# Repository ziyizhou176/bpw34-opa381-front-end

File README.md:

# BPW34 + OPA381 Weak-Signal Photodetector Front-End

KiCad-based, version-controlled redesign of a weak optical signal front-end for physics competition work.

## Final V2 design target

- Photodiode: BPW34
- TIA: OPA381
- Supply input: +5 V
- Analog rail: LP5907-3.3 -> AVDD_3V3
- Reference: REF3312 -> VREF_RAW -> 10 kΩ -> VBIAS_1V25, with local 1 µF bypass
- TIA feedback: 1 MΩ || 15 pF
- ADC isolation/filter: 1 kΩ series + 33 nF to AGND
- Calibration injection: CAL_IN -> 100 MΩ -> normally-open SJCAL -> SUM
- MCU interface: +5V_IN / AGND / ADC_OUT to existing STM32G431 board
- Target modulation/detection: 1 kHz optical modulation, 20 kS/s ADC, digital lock-in / FFT in MCU

## Development policy

This repository replaces GUI-only iterative PCB editing. Every electrical/layout milestone must be committed so that schematic, PCB, and production data can be diffed and rolled back.

Planned milestones:

1. `v0.1-schematic` — clean KiCad schematic, ERC pass, footprint mapping reviewed
2. `v0.2-placement` — critical analog placement frozen
3. `v0.3-critical-routing` — SUM, feedback, VBIAS, OPA381 local decoupling completed
4. `v0.4-full-routing` — remaining power/ADC/CAL routing and ground strategy completed
5. `v1.0-production` — DRC pass, Gerber/BOM/PnP ready for fabrication

## Reference design

Layout principles will be compared against the open hardware project `TU-Darmstadt-APQ/PDH_photodiode`, especially its photodiode/TIA placement, feedback-loop minimization, local decoupling, and ground strategy. The final circuit here is not intended to be an electrical clone; it is redesigned around BPW34, OPA381, 3.3 V single-supply operation, 1.25 V bias, STM32 ADC interfacing, and the calibration network used in this project.

## Status

Repository initialized. Next step: freeze the V2 electrical specification and create the KiCad project skeleton before any PCB routing.

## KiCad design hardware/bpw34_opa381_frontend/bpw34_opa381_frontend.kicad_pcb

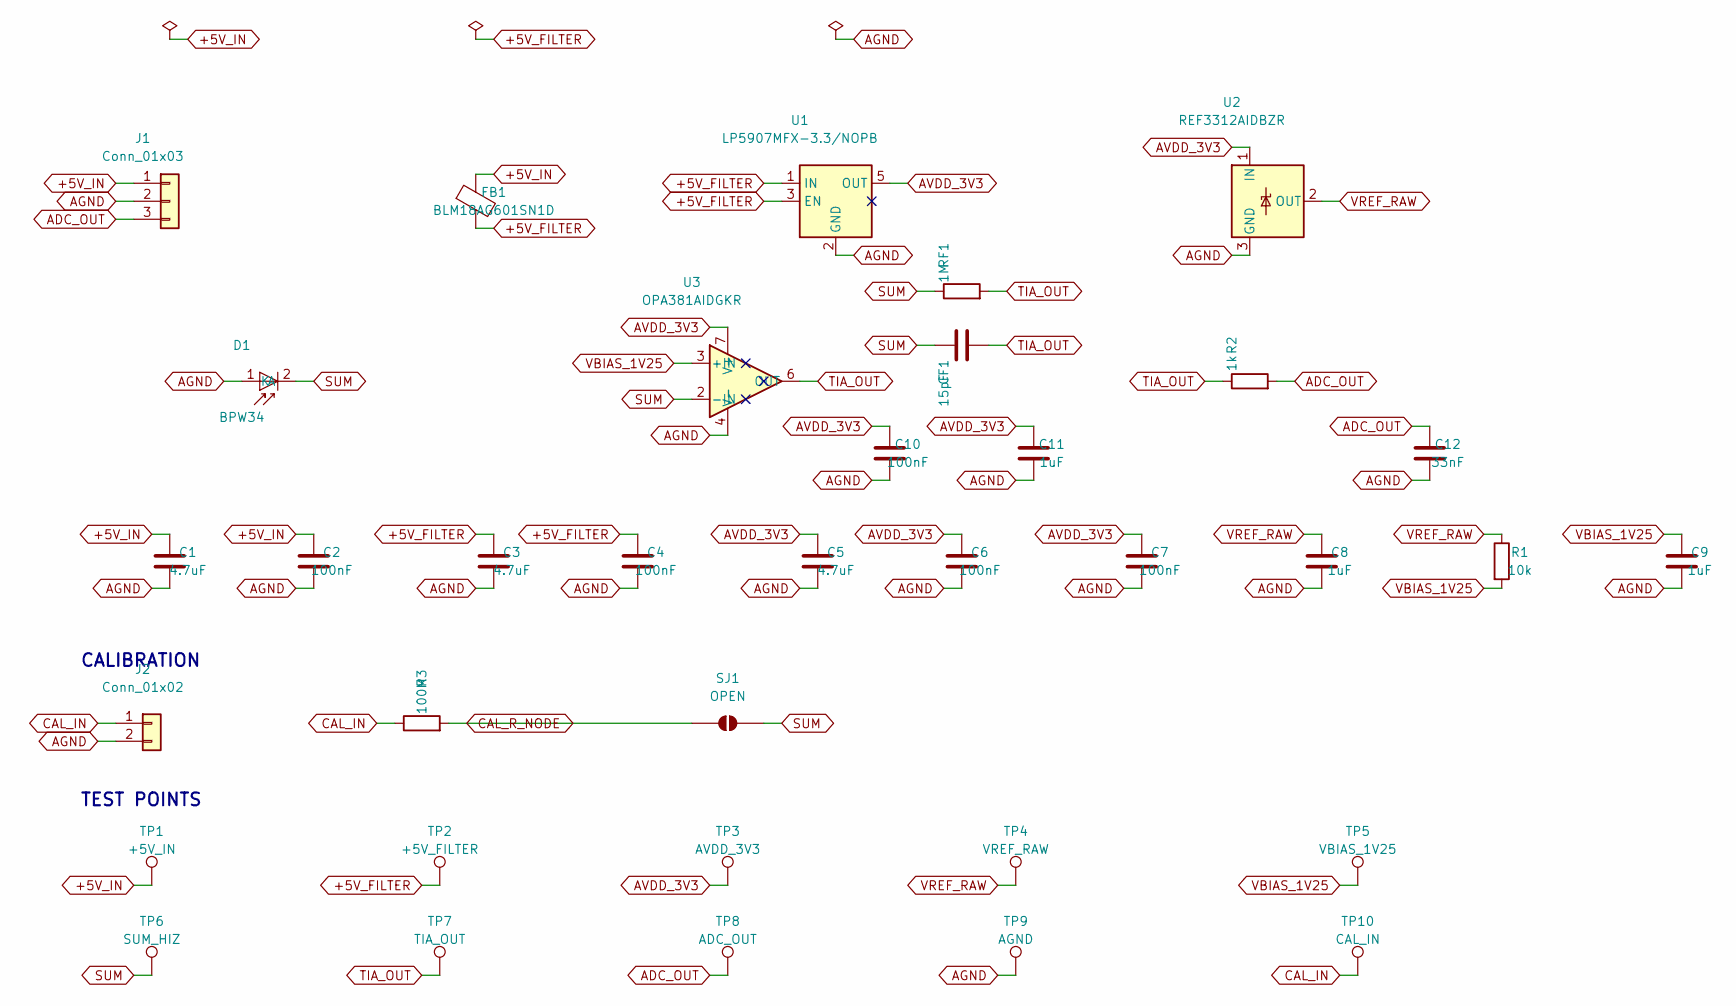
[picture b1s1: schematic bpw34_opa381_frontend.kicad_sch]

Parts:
C1, C3, C5: 4.7uF; C_0603_1608Metric; MPN GRM188Z71C475KE21D; LCSC C389010
C2, C4, C6, C7, C10: 100nF; C_0603_1608Metric; MPN CL10B104KO8NNNC; LCSC C66501
C8, C9, C11: 1uF; C_0603_1608Metric; MPN 0603B105K160CT; LCSC C108463
C12: 33nF; C_0603_1608Metric; MPN CL10B333KB8NNNC; LCSC C21117
CF1: 15pF; C_0603_1608Metric; MPN CL10C150JB8NNNC; LCSC C1644
D1: BPW34; BPW34_Vishay_P5.10mm; MPN BPW34; LCSC C85128
FB1: BLM18AG601SN1D; L_0603_1608Metric; MPN BLM18AG601SN1D; LCSC C19330
J1: Conn_01x03; JST_PH_S3B-PH-SM4-TB_1x03-1MP_P2.00mm_Horizontal; MPN S3B-PH-SM4-TB(LF)(SN); LCSC C265101
J2: Conn_01x02; JST_PH_S2B-PH-SM4-TB_1x02-1MP_P2.00mm_Horizontal; MPN S2B-PH-SM4-TB(LF)(SN); LCSC C295747
R1: 10k; R_0603_1608Metric; Tolerance 0.1%; MPN RT0603BRD0710KL; LCSC C95204
R2: 1k; R_1206_3216Metric; Tolerance 0.1%; MPN RT1206BRD071KL; LCSC C706405
R3: 100M; R_1206_3216Metric; Tolerance 1%; MPN 1206W4F1006T5E; LCSC C59781
RF1: 1M; R_1206_3216Metric; Tolerance 0.1%; MPN RT1206BRD071ML; LCSC C309662
SJ1: OPEN; SolderJumper-2_P1.3mm_Open_RoundedPad1.0x1.5mm
TP1: +5V_IN; TestPoint_Pad_D1.0mm
TP2: +5V_FILTER; TestPoint_Pad_D1.0mm
TP3: AVDD_3V3; TestPoint_Pad_D1.0mm
TP4: VREF_RAW; TestPoint_Pad_D1.0mm
TP5: VBIAS_1V25; TestPoint_Pad_D1.0mm
TP6: SUM_HIZ; TestPoint_Pad_D0.8mm
TP7: TIA_OUT; TestPoint_Pad_D1.2mm
TP8: ADC_OUT; TestPoint_Pad_D1.2mm
TP9: AGND; TestPoint_Pad_D1.2mm
TP10: CAL_IN; TestPoint_Pad_D1.0mm
U1: LP5907MFX-3.3/NOPB; SOT-23-5; MPN LP5907MFX-3.3/NOPB; LCSC C80670
U2: REF3312AIDBZR; SOT-23; MPN REF3312AIDBZR; LCSC C183104
U3: OPA381AIDGKR; VSSOP-8_3x3mm_P0.65mm; MPN OPA381AIDGKR; LCSC C2870973

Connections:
+5V_FILTER: C3.1, C4.1, FB1.2, TP2.1, U1.1 (IN), U1.3 (EN)
+5V_IN: C1.1, C2.1, FB1.1, J1.1, TP1.1
ADC_OUT: C12.2, J1.3, R2.2, TP8.1
AGND: C1.2, C2.2, C3.2, C4.2, C5.2, C6.2, C7.2, C8.2, C9.2, C10.1, C11.1, C12.1, D1.1 (A), J1.2, J2.2, TP9.1, U1.2 (GND), U2.3 (GND), U3.4 (V-)
AVDD_3V3: C5.1, C6.1, C7.1, C10.2, C11.2, TP3.1, U1.5 (OUT), U2.1 (IN), U3.7 (V+)
CAL_IN: J2.1, R3.1, TP10.1
CAL_R_NODE: R3.2, SJ1.1 (A)
SUM: CF1.1, D1.2 (K), RF1.1, SJ1.2 (B), TP6.1, U3.2 (-IN)
TIA_OUT: CF1.2, R2.1, RF1.2, TP7.1, U3.6 (OUT)
VBIAS_1V25: C9.1, R1.2, TP5.1, U3.3 (+IN)
VREF_RAW: C8.1, R1.1, TP4.1, U2.2 (OUT)

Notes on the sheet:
CALIBRATION
TEST POINTS

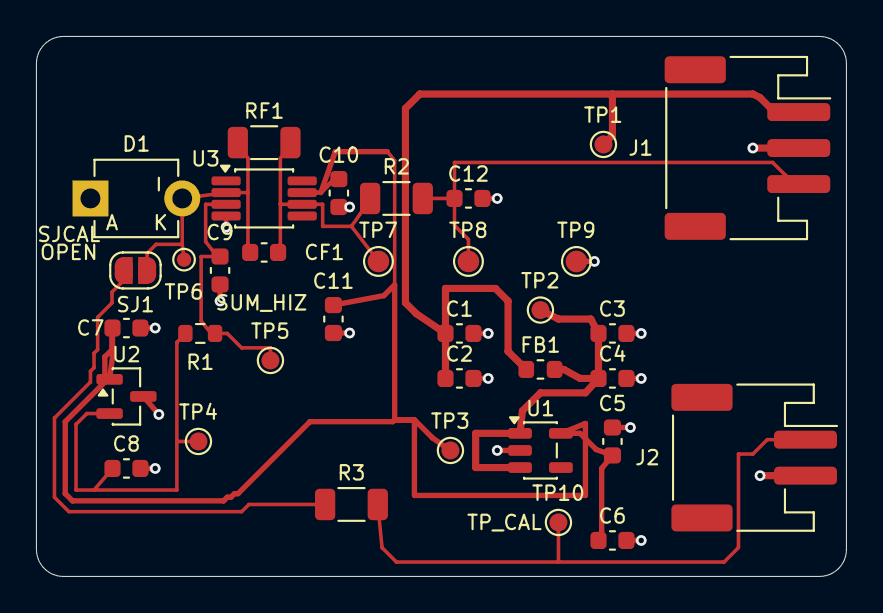
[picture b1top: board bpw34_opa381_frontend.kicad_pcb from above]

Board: 2 copper layers, 45.0 x 30.0 mm, 35 parts (0 on the bottom side), 11 nets.
